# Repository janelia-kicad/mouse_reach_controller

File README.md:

- [Repository Information](#orged9303f)
  - [Description](#org6014a84)
- [Images](#orgde338b6)
- [Schematic](#orgc5988fc)
- [Gerbers](#org908cc94)
- [Bill of Materials](#org2632b07)
  - [PCB Parts](#orgf400c52)
  - [Supplemental Parts](#orga37590c)
  - [Vendor Parts Lists](#orga960ea9)
- [Supplemental Documentation](#org85c6311)
  - [Assembly Instructions](#org5078262)
- [Manufacturing Archive](#org1d40da5)
- [Development](#orgc77368c)

# Repository Information

-   **Name:** mouse\_reach\_controller
-   **Version:** 1.2
-   **License:** Open-Source Hardware
-   **URL:** <https://github.com/janelia-kicad/mouse_reach_controller>
-   **Author:** Peter Polidoro
-   **Email:** peter@polidoro.io

## Description

This board controls the Hantman lab PelletDispenser rig and the RotaryDisk rig.

# Images

# Schematic

[./schematic/mouse\_reach\_controller.pdf](./schematic/mouse_reach_controller.pdf)\n

\n \n \n \n \n \n \n \n \n

# Gerbers

\n \n \n

# Bill of Materials

## PCB Parts

| Item | Reference(s)                                                                                                                   | Quantity | Manufacturer                    | Manufacturer Part Number | Vendor   | Vendor Part Number        | Description                                         | Package |
|---- |------------------------------------------------------------------------------------------------------------------------------ |-------- |------------------------------- |------------------------ |-------- |------------------------- |--------------------------------------------------- |------- |
| 1    | C1 C2 C3 C5 C7 C10 C11 C13 C15 C20 C22 C23 C24 C25 C26 C27 C28 C29 C30 C31 C32 C33 C34 C35 C36 C37 C38 C39 C40 C41 C42 C43 C44 | 33       | Yageo                           | CC0402ZRY5V8BB104        | Digi-Key | 311-1375-1-ND             | CAP CER 0.1UF 25V Y5V                               | 0402    |
| 2    | C9 C18                                                                                                                         | 2        | Panasonic Electronic Components | EEE-FN1V101XV            | Digi-Key | 10-EEE-FN1V101XVCT-ND     | CAP ALUM 100UF 20% 35V                              |         |
| 3    | C12 C14 C16 C19 C21                                                                                                            | 5        | TDK Corporation                 | C1005X5R1V225K050BC      | Digi-Key | 445-9028-1-ND             | CAP CER 2.2UF 35V X5R                               | 0402    |
| 4    | C17                                                                                                                            | 1        | YAGEO                           | CC0402KRX5R7BB154        | Digi-Key | 13-CC0402KRX5R7BB154CT-ND | CAP CER 0.15UF 16V X5R                              | 0402    |
| 5    | CLK1                                                                                                                           | 1        | Würth Elektronik                | 831068248                | Digi-Key | 732-831068248CT-ND        | XTAL OSC XO 32.0000MHZ CMOS                         |         |
| 6    | CLK2                                                                                                                           | 1        | Würth Elektronik                | 831066629                | Digi-Key | 732-831066629CT-ND        | XTAL OSC XO 16.0000MHZ CMOS                         |         |
| 7    | D1 D2                                                                                                                          | 2        | Nexperia USA Inc.               | PMEG45U10EPDAZ           | Digi-Key | 1727-7645-1-ND            | DIODE SCHOTTKY 45V 10A                              | CFP15   |
| 8    | I1                                                                                                                             | 1        | Murata Electronics              | BLM15PX601SN1D           | Digi-Key | 490-9657-1-ND             | FERRITE BEAD 600 OHM                                | 0402    |
| 9    | J1                                                                                                                             | 1        | CUI Devices                     | SJ-3523-SMT-TR           | Digi-Key | CP-3523SJCT-ND            | 3.50mm Headphone Phone Jack Stereo Connector Solder |         |
| 10   | L1 L2 L3 L4 L5 L6 L7                                                                                                           | 7        | Kingbright                      | APHHS1005LSECK/J3-PF     | Digi-Key | 754-2123-1-ND             | LED RED CLEAR 2SMD                                  | 0402    |
| 11   | P1 P2 P3                                                                                                                       | 3        | 3M                              | N3793-6302RB             | Digi-Key | MHS10N-ND                 | CONN HEADER VERT 10POS 2.54MM                       |         |
| 12   | P4                                                                                                                             | 1        | CUI Devices                     | PJ-036AH-SMT-TR          | Digi-Key | CP-036AHPJCT-ND           | CONN PWR JACK 2X5.5MM SOLDER                        |         |
| 13   | P5 P6 P7                                                                                                                       | 3        | Amphenol RF                     | 112661                   | Digi-Key | ACX1655-ND                | CONN BNC JACK R/A 75 OHM PCB                        |         |
| 14   | R1 R17 R18 R19 R20                                                                                                             | 5        | YAGEO                           | RC0402FR-071K6L          | Digi-Key | YAG3045CT-ND              | RES 1.6K OHM 1% 1/16W                               | 0402    |
| 15   | R2 R3 R4 R5 R6 R7                                                                                                              | 6        | Stackpole Electronics Inc       | RMCF0402FT100R           | Digi-Key | RMCF0402FT100RCT-ND       | RES 100 OHM 1% 1/16W                                | 0402    |
| 16   | R8 R9 R10 R11                                                                                                                  | 4        | YAGEO                           | RC0402FR-072K21L         | Digi-Key | 311-2.21KLRCT-ND          | RES 2.21K OHM 1% 1/16W                              | 0402    |
| 17   | R12 R13 R14 R15 R16                                                                                                            | 5        | YAGEO                           | RC0402JR-0710KL          | Digi-Key | 311-10KJRCT-ND            | RES SMD 10K OHM 5% 1/10W                            | 0402    |
| 18   | R21 R22 R23                                                                                                                    | 3        | YAGEO                           | RC0402FR-071KL           | Digi-Key | 311-1.00KLRCT-ND          | RES SMD 1K OHM 1% 1/16W                             | 0402    |
| 19   | T1                                                                                                                             | 1        | Phoenix Contact                 | 1757242                  | Digi-Key | 277-1106-ND               | TERM BLOCK HDR 2POS 90DEG 5.08MM                    |         |
| 20   | T2                                                                                                                             | 1        | Phoenix Contact                 | 1757268                  | Digi-Key | 277-1108-ND               | TERM BLOCK HDR 4POS 90DEG 5.08MM                    |         |
| 21   | TEENSY1                                                                                                                        | 28       | Mill-Max Manufacturing Corp.    | 0305-0-15-15-47-27-10-0  | Digi-Key | ED90331-ND                | CONN PIN RCPT .025-.037 SOLDER                      |         |
| 22   | U1                                                                                                                             | 1        | Trinamic Motion Control GmbH    | TMC429-LI-T              | Digi-Key | 1460-1071-1-ND            | IC MOTOR CONTROLLER SPI 32QFN                       |         |
| 23   | U2 U4 U6                                                                                                                       | 3        | Texas Instruments               | SN65LVDM050QDRQ1         | Digi-Key | 296-15386-1-ND            | IC TRANSCEIVER FULL 2/2                             | 16-SOIC |
| 24   | U8                                                                                                                             | 1        | Diodes Incorporated             | ZXMS6006SGTA             | Digi-Key | ZXMS6006SGTADICT-ND       | IC PWR DRIVER N-CHAN 1:1                            | SOT223  |
| 25   | U9 U11                                                                                                                         | 2        | Richtek USA Inc.                | RT9076-15GV              | Digi-Key | 1028-1470-1-ND            | IC REG LINEAR 1.5V 250MA                            | SOT23-3 |
| 26   | U10                                                                                                                            | 1        | NXP USA Inc.                    | SGTL5000XNAA3R2          | Digi-Key | SGTL5000XNAA3R2CT-ND      | Stereo Audio Interface 32-QFN                       |         |
| 27   | U12 U13 U15 U16 U17 U18 U19 U20                                                                                                | 8        | Nexperia USA Inc.               | 74LVC1G125GS,132         | Digi-Key | 1727-8033-1-ND            | IC BUF NON-INVERT 5.5V                              | 6-XFDFN |
| 28   | U14                                                                                                                            | 1        | Trinamic Motion Control GmbH    | TMC424                   | Digi-Key | 1460-1046-ND              | IC INTERFACE SPECIALIZED                            |         |
|      | FID1 FID2 FID3 FID4 MH1 MH2 MH3 MH4                                                                                            | 8        |                                 |                          |          |                           |                                                     |         |

## Supplemental Parts

| Item | Quantity | Manufacturer                   | Manufacturer Part Number | Vendor   | Vendor Part Number | Description                                       |
|---- |-------- |------------------------------ |------------------------ |-------- |------------------ |------------------------------------------------- |
| 1    | 1        | SparkFun Electronics           | DEV-15583                | Digi-Key | 1568-DEV-15583-ND  | TEENSY 4.0                                        |
| 2    | 2        | TE Connectivity AMP Connectors | 6-146280-4               | Digi-Key | A128925-ND         | CONN HEADER VERT 14POS 2.54MM                     |
| 3    | 1        | Assmann WSW Components         | AK67421-2                | Digi-Key | AE10342-ND         | CBL USB2.0 A PLG-MCR B PLG 6.56FT                 |
| 4    | 1        | CUI Inc.                       | SDI18-5-UC-P5            | Digi-Key | 102-3672-ND        | AC/DC DESKTOP ADAPTER 5V 15W                      |
| 5    | 1        | CUI Devices                    | AC-C13 NA                | Digi-Key | T1249-C13-NA-ND    | CORD 18AWG NEMA5-15P - IEC320 6FT                 |
| 6    | 1        | Phoenix Contact                | 1757019                  | Digi-Key | 277-1011-ND        | TERM BLOCK PLUG 2POS STR 5.08MM                   |
| 7    | 1        | Phoenix Contact                | 1757035                  | Digi-Key | 277-1013-ND        | TERM BLOCK PLUG 4POS STR 5.08MM                   |
| 8    | 1        | Logitech                       | 130 Compact Speakers     | Amazon   | Z130               | Logitech 3.5mm Jack Compact Laptop Speakers Black |

## Vendor Parts Lists

[./bom/Digi-Key\_parts.csv](./bom/Digi-Key_parts.csv)\n [./bom/supplemental\_Amazon\_parts.csv](./bom/supplemental_Amazon_parts.csv)\n [./bom/supplemental\_Digi-Key\_parts.csv](./bom/supplemental_Digi-Key_parts.csv)\n

# Supplemental Documentation

## Assembly Instructions

-   Solder surface mount and through hole components onto the pcb.

# Manufacturing Archive

Send manufacturing zip file to your favorite PCB manufacturer for fabrication.\n [./manufacturing/mouse\_reach\_controller\_v1.2.zip](./manufacturing/mouse_reach_controller_v1.2.zip)\n

# Development

```sh
guix time-machine -C .channels.scm -- shell -m .manifest.scm
```

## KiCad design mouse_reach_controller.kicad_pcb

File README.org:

# Created 2022-11-03 Thu 10:33
#+options: title:nil author:nil email:nil toc:t |:t ^:nil
* Repository Information

- Name :: mouse_reach_controller
- Version :: 1.2
- License :: Open-Source Hardware
- URL :: https://github.com/janelia-kicad/mouse_reach_controller
- Author :: Peter Polidoro
- Email :: peter@polidoro.io

** Description

This board controls the Hantman lab PelletDispenser rig and the RotaryDisk rig.

* Images

* Schematic

[[file:./schematic/mouse_reach_controller.pdf][./schematic/mouse_reach_controller.pdf]]\n

[[file:./schematic/images/schematic00.png]]\n
[[file:./schematic/images/schematic01.png]]\n
[[file:./schematic/images/schematic02.png]]\n
[[file:./schematic/images/schematic03.png]]\n
[[file:./schematic/images/schematic04.png]]\n
[[file:./schematic/images/schematic05.png]]\n
[[file:./schematic/images/schematic06.png]]\n
[[file:./schematic/images/schematic07.png]]\n
[[file:./schematic/images/schematic08.png]]\n

* Gerbers

[[file:./gerbers/images/mouse_reach_controller-B_SilkS.png]]\n
[[file:./gerbers/images/mouse_reach_controller-Dwgs_User.png]]\n
[[file:./gerbers/images/mouse_reach_controller-F_SilkS.png]]\n

* Bill of Materials

** PCB Parts

| Item | Reference(s)                                                                                                                   | Quantity | Manufacturer                    | Manufacturer Part Number | Vendor   | Vendor Part Number        | Description                                         | Package |
|------+--------------------------------------------------------------------------------------------------------------------------------+----------+---------------------------------+--------------------------+----------+---------------------------+-----------------------------------------------------+---------|
|    1 | C1 C2 C3 C5 C7 C10 C11 C13 C15 C20 C22 C23 C24 C25 C26 C27 C28 C29 C30 C31 C32 C33 C34 C35 C36 C37 C38 C39 C40 C41 C42 C43 C44 |       33 | Yageo                           | CC0402ZRY5V8BB104        | Digi-Key | 311-1375-1-ND             | CAP CER 0.1UF 25V Y5V                               |    0402 |
|    2 | C9 C18                                                                                                                         |        2 | Panasonic Electronic Components | EEE-FN1V101XV            | Digi-Key | 10-EEE-FN1V101XVCT-ND     | CAP ALUM 100UF 20% 35V                              |         |
|    3 | C12 C14 C16 C19 C21                                                                                                            |        5 | TDK Corporation                 | C1005X5R1V225K050BC      | Digi-Key | 445-9028-1-ND             | CAP CER 2.2UF 35V X5R                               |    0402 |
|    4 | C17                                                                                                                            |        1 | YAGEO                           | CC0402KRX5R7BB154        | Digi-Key | 13-CC0402KRX5R7BB154CT-ND | CAP CER 0.15UF 16V X5R                              |    0402 |
|    5 | CLK1                                                                                                                           |        1 | Würth Elektronik                | 831068248                | Digi-Key | 732-831068248CT-ND        | XTAL OSC XO 32.0000MHZ CMOS                         |         |
|    6 | CLK2                                                                                                                           |        1 | Würth Elektronik                | 831066629                | Digi-Key | 732-831066629CT-ND        | XTAL OSC XO 16.0000MHZ CMOS                         |         |
|    7 | D1 D2                                                                                                                          |        2 | Nexperia USA Inc.               | PMEG45U10EPDAZ           | Digi-Key | 1727-7645-1-ND            | DIODE SCHOTTKY 45V 10A                              |   CFP15 |
|    8 | I1                                                                                                                             |        1 | Murata Electronics              | BLM15PX601SN1D           | Digi-Key | 490-9657-1-ND             | FERRITE BEAD 600 OHM                                |    0402 |
|    9 | J1                                                                                                                             |        1 | CUI Devices                     | SJ-3523-SMT-TR           | Digi-Key | CP-3523SJCT-ND            | 3.50mm Headphone Phone Jack Stereo Connector Solder |         |
|   10 | L1 L2 L3 L4 L5 L6 L7                                                                                                           |        7 | Kingbright                      | APHHS1005LSECK/J3-PF     | Digi-Key | 754-2123-1-ND             | LED RED CLEAR 2SMD                                  |    0402 |
|   11 | P1 P2 P3                                                                                                                       |        3 | 3M                              | N3793-6302RB             | Digi-Key | MHS10N-ND                 | CONN HEADER VERT 10POS 2.54MM                       |         |
|   12 | P4                                                                                                                             |        1 | CUI Devices                     | PJ-036AH-SMT-TR          | Digi-Key | CP-036AHPJCT-ND           | CONN PWR JACK 2X5.5MM SOLDER                        |         |
|   13 | P5 P6 P7                                                                                                                       |        3 | Amphenol RF                     | 112661                   | Digi-Key | ACX1655-ND                | CONN BNC JACK R/A 75 OHM PCB                        |         |
|   14 | R1 R17 R18 R19 R20                                                                                                             |        5 | YAGEO                           | RC0402FR-071K6L          | Digi-Key | YAG3045CT-ND              | RES 1.6K OHM 1% 1/16W                               |    0402 |
|   15 | R2 R3 R4 R5 R6 R7                                                                                                              |        6 | Stackpole Electronics Inc       | RMCF0402FT100R           | Digi-Key | RMCF0402FT100RCT-ND       | RES 100 OHM 1% 1/16W                                |    0402 |
|   16 | R8 R9 R10 R11                                                                                                                  |        4 | YAGEO                           | RC0402FR-072K21L         | Digi-Key | 311-2.21KLRCT-ND          | RES 2.21K OHM 1% 1/16W                              |    0402 |
|   17 | R12 R13 R14 R15 R16                                                                                                            |        5 | YAGEO                           | RC0402JR-0710KL          | Digi-Key | 311-10KJRCT-ND            | RES SMD 10K OHM 5% 1/10W                            |    0402 |
|   18 | R21 R22 R23                                                                                                                    |        3 | YAGEO                           | RC0402FR-071KL           | Digi-Key | 311-1.00KLRCT-ND          | RES SMD 1K OHM 1% 1/16W                             |    0402 |
|   19 | T1                                                                                                                             |        1 | Phoenix Contact                 | 1757242                  | Digi-Key | 277-1106-ND               | TERM BLOCK HDR 2POS 90DEG 5.08MM                    |         |
|   20 | T2                                                                                                                             |        1 | Phoenix Contact                 | 1757268                  | Digi-Key | 277-1108-ND               | TERM BLOCK HDR 4POS 90DEG 5.08MM                    |         |
|   21 | TEENSY1                                                                                                                        |       28 | Mill-Max Manufacturing Corp.    | 0305-0-15-15-47-27-10-0  | Digi-Key | ED90331-ND                | CONN PIN RCPT .025-.037 SOLDER                      |         |
|   22 | U1                                                                                                                             |        1 | Trinamic Motion Control GmbH    | TMC429-LI-T              | Digi-Key | 1460-1071-1-ND            | IC MOTOR CONTROLLER SPI 32QFN                       |         |
|   23 | U2 U4 U6                                                                                                                       |        3 | Texas Instruments               | SN65LVDM050QDRQ1         | Digi-Key | 296-15386-1-ND            | IC TRANSCEIVER FULL 2/2                             | 16-SOIC |
|   24 | U8                                                                                                                             |        1 | Diodes Incorporated             | ZXMS6006SGTA             | Digi-Key | ZXMS6006SGTADICT-ND       | IC PWR DRIVER N-CHAN 1:1                            |  SOT223 |
|   25 | U9 U11                                                                                                                         |        2 | Richtek USA Inc.                | RT9076-15GV              | Digi-Key | 1028-1470-1-ND            | IC REG LINEAR 1.5V 250MA                            | SOT23-3 |
|   26 | U10                                                                                                                            |        1 | NXP USA Inc.                    | SGTL5000XNAA3R2          | Digi-Key | SGTL5000XNAA3R2CT-ND      | Stereo Audio Interface 32-QFN                       |         |
|   27 | U12 U13 U15 U16 U17 U18 U19 U20                                                                                                |        8 | Nexperia USA Inc.               | 74LVC1G125GS,132         | Digi-Key | 1727-8033-1-ND            | IC BUF NON-INVERT 5.5V                              | 6-XFDFN |
|   28 | U14                                                                                                                            |        1 | Trinamic Motion Control GmbH    | TMC424                   | Digi-Key | 1460-1046-ND              | IC INTERFACE SPECIALIZED                            |         |
|      | FID1 FID2 FID3 FID4 MH1 MH2 MH3 MH4                                                                                            |        8 |                                 |                          |          |                           |                                                     |         |

** Supplemental Parts

| Item | Quantity | Manufacturer                   | Manufacturer Part Number | Vendor   | Vendor Part Number | Description                                       |
|------+----------+--------------------------------+--------------------------+----------+--------------------+---------------------------------------------------|
|    1 |        1 | SparkFun Electronics           | DEV-15583                | Digi-Key | 1568-DEV-15583-ND  | TEENSY 4.0                                        |
|    2 |        2 | TE Connectivity AMP Connectors | 6-146280-4               | Digi-Key | A128925-ND         | CONN HEADER VERT 14POS 2.54MM                     |
|    3 |        1 | Assmann WSW Components         | AK67421-2                | Digi-Key | AE10342-ND         | CBL USB2.0 A PLG-MCR B PLG 6.56FT                 |
|    4 |        1 | CUI Inc.                       | SDI18-5-UC-P5            | Digi-Key | 102-3672-ND        | AC/DC DESKTOP ADAPTER 5V 15W                      |
|    5 |        1 | CUI Devices                    | AC-C13 NA                | Digi-Key | T1249-C13-NA-ND    | CORD 18AWG NEMA5-15P - IEC320 6FT                 |
|    6 |        1 | Phoenix Contact                | 1757019                  | Digi-Key | 277-1011-ND        | TERM BLOCK PLUG 2POS STR 5.08MM                   |
|    7 |        1 | Phoenix Contact                | 1757035                  | Digi-Key | 277-1013-ND        | TERM BLOCK PLUG 4POS STR 5.08MM                   |
|    8 |        1 | Logitech                       | 130 Compact Speakers     | Amazon   | Z130               | Logitech 3.5mm Jack Compact Laptop Speakers Black |
#+TBLFM: $1=@#-1

** Vendor Parts Lists

[[file:./bom/Digi-Key_parts.csv][./bom/Digi-Key_parts.csv]]\n
[[file:./bom/supplemental_Amazon_parts.csv][./bom/supplemental_Amazon_parts.csv]]\n
[[file:./bom/supplemental_Digi-Key_parts.csv][./bom/supplemental_Digi-Key_parts.csv]]\n

* Supplemental Documentation

** Assembly Instructions

- Solder surface mount and through hole components onto the pcb.

* Manufacturing Archive

Send manufacturing zip file to your favorite PCB manufacturer for fabrication.\n
[[file:./manufacturing/mouse_reach_controller_v1.2.zip][./manufacturing/mouse_reach_controller_v1.2.zip]]\n

* Development

#+begin_src sh
  guix time-machine -C .channels.scm -- shell -m .manifest.scm
#+end_src

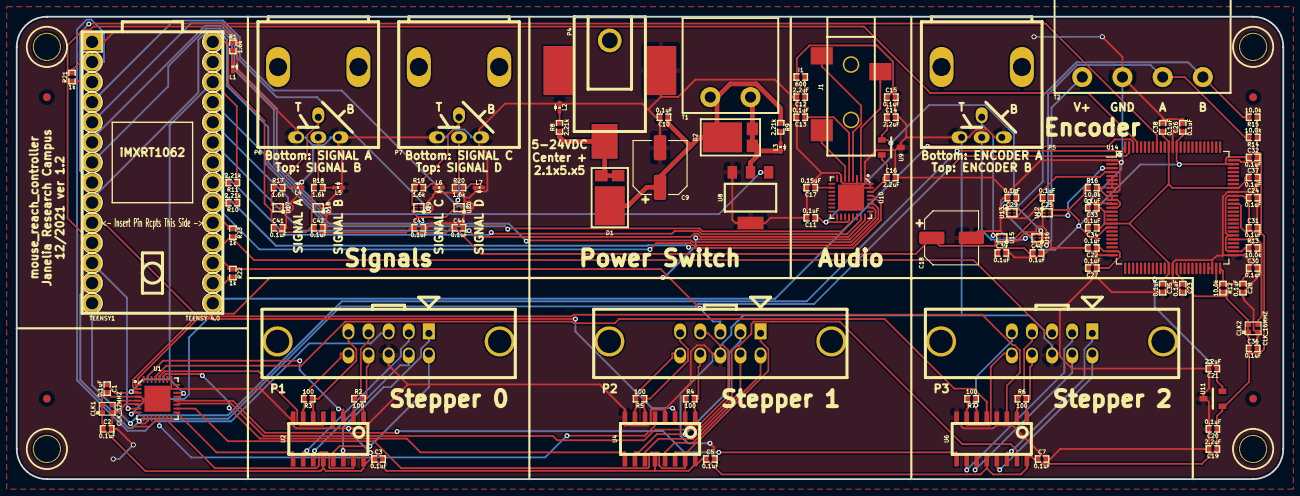
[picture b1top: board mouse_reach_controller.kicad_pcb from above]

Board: 2 copper layers, 160.0 x 58.4 mm, 112 parts (0 on the bottom side), 95 nets.

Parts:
C1, C2, C3, C5, C7, C10, C11, C13, C15, C20, C22, C23, C24, C25, C26, C27, C28, C29, C30, C31, C32, C33, C34, C35, C36, C37, C38, C39, C40, C41, C42, C43, C44: 0.1uF; SM0402
C9: 100uF; CP_Elec_6.3x8.3_PAN
C12, C14, C16, C19, C21: 2.2uF; SM0402
C17: 0.15uF; SM0402
C18: 100uF_POL; CP_Elec_6.3x8.3_PAN
CLK1: CLK_32MHZ; XTAL_WURTH
CLK2: CLK_16MHZ; XTAL_WURTH
D1, D2: DIODE_SCHOTTKY_45V_10A; CFP15
FID1, FID2, FID3, FID4: FIDUCIAL_1.0mm_MASK2mm; Fiducial_1mm_Mask2mm
I1: 600; SM0402
J1: AUDIO_JACK_3.5MM; AUDIO_JACK_3.5MM_3PIN
L1, L2, L3, L4, L5, L6, L7: LED; LED_0402
MH1, MH2, MH3, MH4: MOUNTING_HOLE_4-40
P1, P2, P3: HEADER_02X05_LATCH; HEADER_02x05_LATCH
P4: PWR_JACK_2.1x5.5_SMD_RA; DCJACK_3PAD_SMD_RA
P5, P6, P7: BNC_DOUBLE_RA; BNC_DOUBLE
R1, R17, R18, R19, R20: 1.6k; SM0402
R2, R3, R4, R5, R6, R7: 100; SM0402
R8, R9, R10, R11: 2.21k; SM0402
R12, R13, R14, R15, R16: 10.0k; SM0402
R21, R22, R23: 1k; SM0402
T1: TERM_BLK_HDR_2POS_90DEG_0.2IN
T2: TERM_BLK_HDR_4POS_90DEG_0.2IN
TEENSY1: TEENSY_4.0_PIN_RECEPTACLES
U1: TMC429; QFN-32-1EP_5x5mm_P0.5mm_EP3.3x3.3mm
U2, U4, U6: SN65LVDM050QDRQ1; SOIC_16_0.154IN
U8: ZXMS6006SG; SOT-223-3
U9, U11: RT9076-15GV; SOT-23-3
U10: SGTL5000; QFN-32-1EP_5x5mm_P0.5mm_EP3.3x3.3mm
U12, U13, U15, U16, U17, U18, U19, U20: 74LVC1G125GS; SOT1202
U14: TMC424; TQFP-100_14x14mm_P0.5mm

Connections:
/BCLK: TEENSY1.21, U10.24
/GND: C1.2, C2.2, C3.2, C5.2, C7.2, C9.2, C10.2, C11.2, C12.2, C13.2, C14.2, C15.2, C16.2, C17.2, C18.2, C19.2, C20.2, C21.2, C22.2, C23.2, C24.2, C25.2, C26.2, C27.2, C28.2, C29.2, C30.2, C31.2, C32.2, C33.2, C34.2, C35.2, C36.2, C37.2, C38.2, C39.2, C40.2, C41.2, C42.2, C43.2, C44.2, CLK1.2, CLK2.2, L1.1, L2.1, L4.1, L5.1, L6.1, L7.1, P1.6, P2.6, P3.6, P4.2, P5.2, P5.4, P6.2, P6.4, P7.2, P7.4, T2.2, TEENSY1.GND, U1.4, U1.6, U1.23, U1.25, U1.33, U2.4, U2.8, U4.4, U4.8, U6.4, U6.8, U8.3, U8.4, U9.3, U10.1, U10.3, U10.7, U10.31, U10.32, U10.33, U11.3, U12.1, U12.3, U13.1, U13.3, U14.1, U14.9, U14.12, U14.25, U14.38, U14.47, U14.48, U14.51, U14.67, U14.75, U14.88, U15.1, U15.3, U16.1, U16.3, U17.1, U17.3, U18.1, U18.3, U19.1, U19.3, U20.1, U20.3
/I2S_DIN: TEENSY1.7, U10.26
/I2S_DOUT: TEENSY1.8, U10.25
/LRCLK: TEENSY1.20, U10.23
/MCLK: TEENSY1.23, U10.21
/MISO: TEENSY1.12, U1.12, U14.100
/MOSI: TEENSY1.11, U1.10, U14.99
/POWER_SWITCH_ENABLE: TEENSY1.5, U8.1
/SCK: TEENSY1.13, U1.8, U14.98
/SCL: R11.2, TEENSY1.19, U10.29
/SDA: R10.2, TEENSY1.18, U10.27
/SIGNAL_A: TEENSY1.22, U17.2
/SIGNAL_B: TEENSY1.4, U18.2
/SIGNAL_C: TEENSY1.3, U19.2
/SIGNAL_D: TEENSY1.2, U20.2
/UART_CPU_RX_0: P1.5, R21.2, TEENSY1.0
/UART_CPU_RX_1: P2.5, R22.2, TEENSY1.15
/UART_CPU_RX_2: P3.5, R23.2, TEENSY1.16
/UART_CPU_TX_0: R21.1, TEENSY1.1
/UART_CPU_TX_1: R22.1, TEENSY1.14
/UART_CPU_TX_2: R23.1, TEENSY1.17
/VCC: C18.1, C39.1, C40.1, C41.1, C42.1, C43.1, C44.1, R1.1, T2.1, TEENSY1.V, U15.6, U16.6, U17.6, U18.6, U19.6, U20.6
/VDD: C1.1, C2.1, C3.1, C5.1, C7.1, C11.1, C14.1, C15.1, C19.1, C20.1, C22.1, C23.1, C24.1, C25.1, C26.1, C27.1, C28.1, C29.1, C30.1, C31.1, C32.1, C36.1, CLK1.1, CLK1.4, CLK2.1, CLK2.4, I1.1, R10.1, R11.1, R12.1, R13.1, R14.1, R15.1, R16.1, TEENSY1.3V3, U1.3, U1.21, U1.22, U2.12, U2.16, U4.12, U4.16, U6.12, U6.16, U9.1, U10.20, U11.1, U12.6, U13.6, U14.18, U14.24, U14.39, U14.50, U14.52, U14.56, U14.66, U14.74, U14.87
/audio_controller/HP_L: J1.2, U10.6
/audio_controller/HP_R: J1.3, U10.2
/audio_controller/HP_VGND: J1.1, U10.4
/audio_controller/VAG: C17.1, U10.10
/audio_controller/VEE: C16.1, U9.2, U10.30
/encoder_interface/CHANNEL_A: R14.2, T2.3, U12.2, U15.2
/encoder_interface/CHANNEL_A_OUT: P5.1, U15.4
/encoder_interface/CHANNEL_A_TMC424: U12.4, U14.3
/encoder_interface/CHANNEL_B: R15.2, T2.4, U13.2, U16.2
/encoder_interface/CHANNEL_B_OUT: P5.3, U16.4
/encoder_interface/CHANNEL_B_TMC424: U13.4, U14.4
/encoder_interface/CLK: CLK2.3, U14.64
/encoder_interface/VDD_PULLUP: R16.2, U14.5, U14.6, U14.7, U14.8, U14.10, U14.11, U14.13
/encoder_interface/VEE: C21.1, C33.1, C34.1, C35.1, C37.1, C38.1, U11.2, U14.14, U14.17, U14.37, U14.68, U14.89
/power_switch_driver/OUT: D2.2, L3.1, T1.2, U8.2
/power_switch_driver/VAA: D1.2, P4.1, R8.1
/power_switch_driver/VBB: C9.1, C10.1, D1.1, D2.1, R9.1, T1.1
/signal_interface/SIGNAL_A_BUF: P6.1, R17.1, U17.4
/signal_interface/SIGNAL_B_BUF: P6.3, R18.1, U18.4
/signal_interface/SIGNAL_C_BUF: P7.1, R19.1, U19.4
/signal_interface/SIGNAL_D_BUF: P7.3, R20.1, U20.4
/stepper_controller/CLK: CLK1.3, U1.5
/stepper_controller/DIR_0: U1.17, U2.9
/stepper_controller/DIR_1: U1.27, U4.9
/stepper_controller/DIR_2: U1.20, U6.9
/stepper_controller/REFR_0: U1.28, U2.5
/stepper_controller/REFR_1: U1.13, U4.5
/stepper_controller/REFR_2: U1.29, U6.5
/stepper_controller/REF_0: U1.31, U2.3
/stepper_controller/REF_1: U1.1, U4.3
/stepper_controller/REF_2: U1.2, U6.3
/stepper_controller/STEP_0: U1.15, U2.15
/stepper_controller/STEP_1: U1.18, U4.15
/stepper_controller/STEP_2: U1.19, U6.15
/stepper_controller/stepper_driver_interface_0/DIR_A: P1.3, U2.10
/stepper_controller/stepper_driver_interface_0/DIR_B: P1.4, U2.11
/stepper_controller/stepper_driver_interface_0/REFR_A: P1.9, R3.1, U2.6
/stepper_controller/stepper_driver_interface_0/REFR_B: P1.10, R3.2, U2.7
/stepper_controller/stepper_driver_interface_0/REF_A: P1.7, R2.1, U2.2
/stepper_controller/stepper_driver_interface_0/REF_B: P1.8, R2.2, U2.1
/stepper_controller/stepper_driver_interface_0/STEP_A: P1.1, U2.14
/stepper_controller/stepper_driver_interface_0/STEP_B: P1.2, U2.13
/stepper_controller/stepper_driver_interface_1/DIR_A: P2.3, U4.10
/stepper_controller/stepper_driver_interface_1/DIR_B: P2.4, U4.11
/stepper_controller/stepper_driver_interface_1/REFR_A: P2.9, R5.1, U4.6
/stepper_controller/stepper_driver_interface_1/REFR_B: P2.10, R5.2, U4.7
/stepper_controller/stepper_driver_interface_1/REF_A: P2.7, R4.1, U4.2
/stepper_controller/stepper_driver_interface_1/REF_B: P2.8, R4.2, U4.1
/stepper_controller/stepper_driver_interface_1/STEP_A: P2.1, U4.14
/stepper_controller/stepper_driver_interface_1/STEP_B: P2.2, U4.13
/stepper_controller/stepper_driver_interface_2/DIR_A: P3.3, U6.10
/stepper_controller/stepper_driver_interface_2/DIR_B: P3.4, U6.11
/stepper_controller/stepper_driver_interface_2/REFR_A: P3.9, R7.1, U6.6
/stepper_controller/stepper_driver_interface_2/REFR_B: P3.10, R7.2, U6.7
/stepper_controller/stepper_driver_interface_2/REF_A: P3.7, R6.1, U6.2
/stepper_controller/stepper_driver_interface_2/REF_B: P3.8, R6.2, U6.1
/stepper_controller/stepper_driver_interface_2/STEP_A: P3.1, U6.14
/stepper_controller/stepper_driver_interface_2/STEP_B: P3.2, U6.13
/~ENCODER_CS: TEENSY1.9, U14.97
/~ENCODER_RESET: TEENSY1.6, U14.92
/~STEPPER_CS: TEENSY1.10, U1.7
unnamed: C12.1, C13.1, I1.2, U10.5
unnamed: L1.2, R1.2
unnamed: L2.2, R8.2
unnamed: L3.2, R9.2
unnamed: L4.2, R17.2
unnamed: L5.2, R18.2
unnamed: L6.2, R19.2
unnamed: L7.2, R20.2
unnamed: R12.2, U14.49
unnamed: R13.2, U14.55

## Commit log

2021-01-04 Update names
2021-08-24 pellet_dispenser -> mouse_reach
2021-09-21 Remove ignored files
2021-11-02 Initial components
2021-11-04 Add stepper driver interface
2021-11-05 Add buzzer driver
2021-11-08 Add audio_controller
2021-11-09 Complete initial version of schematic
2021-11-10 Initial layout
2021-11-11 Finish layout
2021-11-12 Update documentation
2021-11-18 Progress towards v1.1
2021-11-19 Add encoder interface
2021-11-30 Progress towards v1.1 layout
2021-12-01 Added components
2021-12-02 Update footprint text
2021-12-02 Create signal_interface sheet
2021-12-03 Progress towards v1.1 pcb layout
2021-12-03 Route board
2021-12-03 Add fabrication files
2021-12-06 Updated supplemental bom
2021-12-07 Add Digi-Key_order
2021-12-09 Export schematic and board files for manufacturing and assembly
2021-12-15 Update schematics
2021-12-30 Fix missing pin 1 markers on silkscreen
2022-01-05 Clarify pin 1 on more footprints
2022-01-27 Board modifications
2022-02-22 Add guix files
2022-02-22 Update kicad exports
2022-02-23 Add guix documentation
2022-11-03 Update project version
2023-08-16 Remove all files to prepare for version 2
